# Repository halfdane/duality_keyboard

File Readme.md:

# The Duality Keyboard

Generated using ergogen:

There are two options to generate this:
- copy the content of `config/duality_keyboard.yaml` into https://ergogen.cache.works/ and start fiddling
- run `npm install` and `npm run start` (or `npm run watch` for continuous build)

# Install qmk
https://docs.qmk.fm/#/getting_started_make_guide

pamac install qmk

`sudo pacman -Sy base-devel gcc unzip wget zip avr-gcc avr-binutils avr-libc dfu-util arm-none-eabi-gcc arm-none-eabi-binutils arm-none-eabi-newlib git dfu-programmer dfu-util`

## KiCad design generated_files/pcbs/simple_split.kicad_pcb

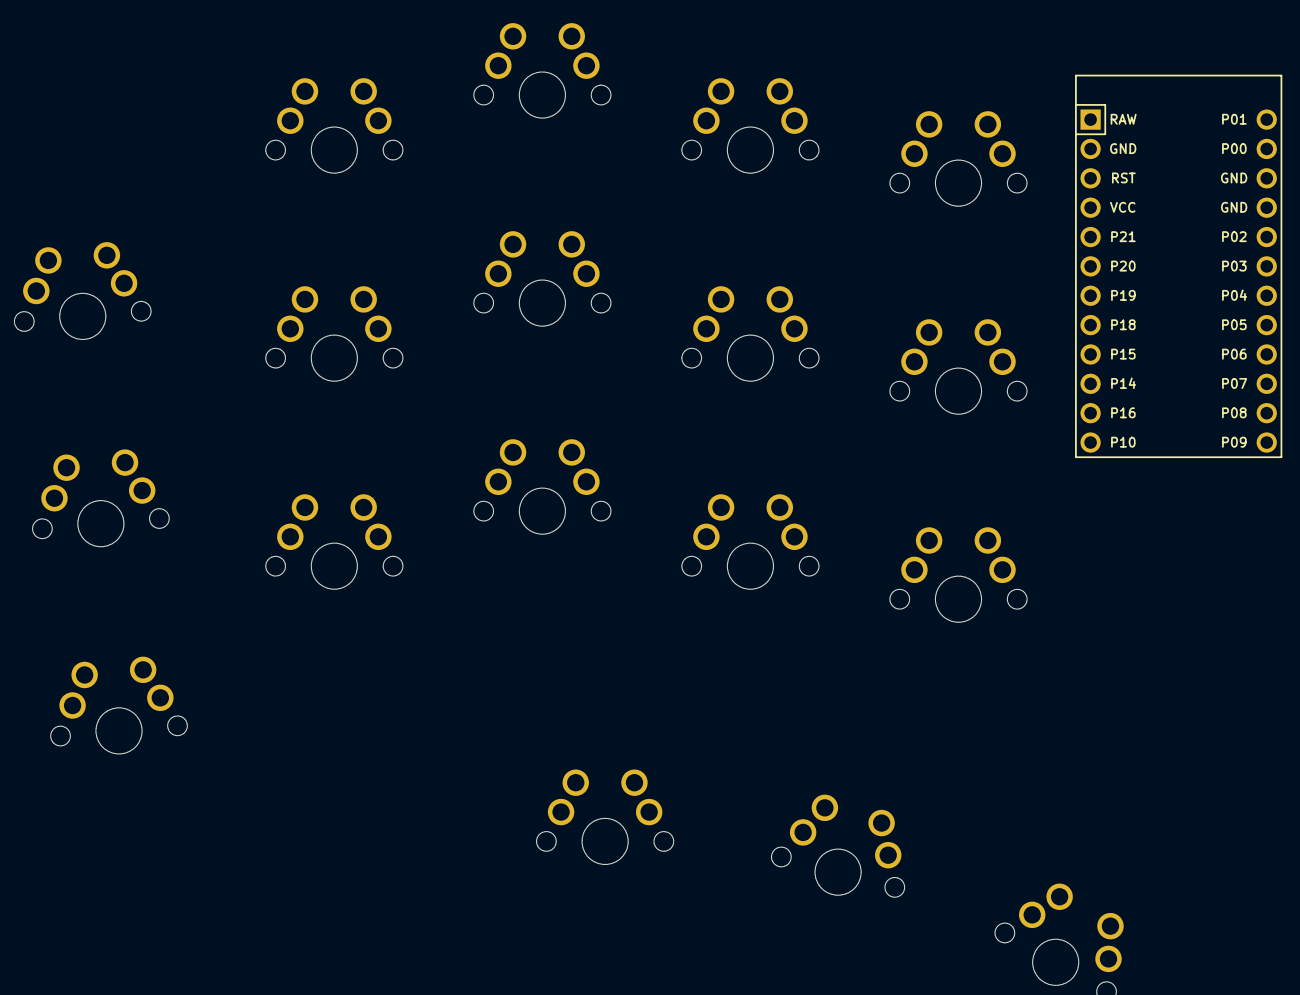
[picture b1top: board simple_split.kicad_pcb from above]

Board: 2 copper layers, 19 parts (0 on the bottom side), 18 nets, no tracks yet.

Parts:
MCU1: ProMicro
S1, S2, S3, S4, S5, S6, S7, S8, S9, S10, S11, S12, S13, S14, S15, S16, S17, S18: MX

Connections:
GND: MCU1.2, MCU1.15, MCU1.16, S1.1, S2.1, S3.1, S4.1, S5.1, S6.1, S7.1, S8.1, S9.1, S10.1, S11.1, S12.1, S13.1, S14.1, S15.1, S16.1, S17.1, S18.1
matrix_index_bottom: MCU1.20, S10.2
matrix_index_home: MCU1.12, S11.2
matrix_index_top: MCU1.6, S12.2
matrix_inner_bottom: MCU1.21, S13.2
matrix_inner_home: MCU1.13, S14.2
matrix_inner_top: MCU1.5, S15.2
matrix_middle_bottom: MCU1.19, S7.2
matrix_middle_home: MCU1.11, S8.2
matrix_middle_top: MCU1.7, S9.2
matrix_pinky_bottom: MCU1.17, S1.2
matrix_pinky_home: MCU1.9, S2.2
matrix_pinky_top: MCU1.22, S3.2
matrix_ring_bottom: MCU1.18, S4.2
matrix_ring_home: MCU1.10, S5.2
matrix_ring_top: MCU1.8, S6.2
thumb_reachy: MCU1.24, S18.2
thumb_tucky: MCU1.23, S16.2

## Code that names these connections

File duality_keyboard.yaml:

# `U` is a predefined unit of measure that means 19.05mm, which is MX spacing
points:
  zones:
    matrix:
      anchor:
        rotate: 5
      columns:
        pinky:
          spread: 1.1cx
        ring:
          rotate: -5
          stagger: 0.66U
          spread: 1.1cx
        middle:
          stagger: 0.25U
          spread: 1.05cx
        index:
          stagger: -0.25U
          spread: 1.05cx
        inner:
          stagger: -0.15U
          spread: 1.05cx
      rows:
        bottom.padding: 1.05cx
        home.padding: 1.05cx
        top.padding: 1.05cx
    thumb:
      anchor:
        ref: matrix_index_bottom
        shift: [-0.4U, -1.25U]
        rotate: 0
      columns:
        tucky:
          key.name: thumb_tucky
        middle:
          key.name: thumb_middle
          origin: [-0.5U, -0.3U]
          rotate: -15
        reachy:
          spread: U
          rotate: -15
          origin: [-0.5U, -0.3U]
          key.name: thumb_reachy
  key:
    footprints:
      - type: mx
        nets:
          from: GND
          to: =name
        params:
          reverse: true
          keycaps: false
outlines:
  exports:
    plate:
      - type: rectangle
        size: [150, 130]
        anchor.shift: [0, -40]
        corner: 10
    keys:
      - type: keys
        side: left
        size: [18,17]
        corner: 1
    touchpad:
      - type: circle
        radius: 19
        anchor.shift: [127, 25]
    intersected_outline:
      - +plate
      - -keys
      - -touchpad
pcbs:
  simple_split:
    footprints:
      - type: promicro
        anchor:
          - ref: matrix_inner_home
            shift: [1U, 0.5U]
            rotate: -90
        nets:
          P7: matrix_pinky_top
          P18: matrix_ring_top
          P19: matrix_middle_top
          P20: matrix_index_top
          P21: matrix_inner_top
          P15: matrix_pinky_home
          P14: matrix_ring_home
          P16: matrix_middle_home
          P10: matrix_index_home
          P1: matrix_inner_home
          P2: matrix_pinky_bottom
          P3: matrix_ring_bottom
          P4: matrix_middle_bottom
          P5: matrix_index_bottom
          P6: matrix_inner_bottom
          P8: thumb_tucky
          P9: thumb_reachy

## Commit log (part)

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2022-06-13 don't add generated files again
2022-06-13 remove generated files from git
2022-06-13 now with touchpad and a plate
2022-06-13 initial layout
2022-06-13 add the right-sized switch holes and a shaped switch plate
2022-06-13 add a little bit of space between keys
2022-06-13 Simple readme
2022-06-14 move trackpad closer to keys
2022-06-14 introduce entry to cable tunnel
2022-06-14 make touchpad-hole slightly larger
2022-06-14 add screw holes
2022-06-14 adjust readme
2022-06-21 use smaller footprint for keys
2022-06-21 reposition keywell and promicro after using smaller caps
2022-09-14 rethink the shape
2022-09-23 enough space for rp2040 zero
2022-09-26 reduce border so it does'nt get **huge**
2022-10-19 ordered the plate at laserboost
2024-05-25 better build pipeline
2024-05-25 several layers and an a3 cutout example
2024-05-27 remove stabilizer sticks
2024-05-27 decide hole sizes
2024-05-29 parameterize symbol
2024-06-02 documentation and layer preparation
2024-06-02 adjust to choc dimensions
2024-06-02 clean up choc top frame
2024-06-07 introduce connector holes
2024-06-08 all layers defined plus some cleanup
2024-06-08 include space for trackpad
2024-06-08 prepare second test burn
2024-06-13 adjust connectors and add touchpad magnet
2024-06-13 add more magnets to the top layers
2024-06-13 adjust rp2040 cutout to keep solder pads usable
2024-06-13 top layer of switch pad doesn't have screw holes - hopefully they can stay below
2024-06-13 consolidate some layers
2024-06-13 new voronoi pattern
2024-06-14 prepare next cut
2024-06-15 simple spoilboard markers to help positioning and focus
2024-06-20 doubling up veneer sheets reduces layer count
2024-06-20 resize the keyboard, change the design and place several components at the right position
2024-06-20 some more connector fiddling
2024-06-20 reposition thumb screws
2024-06-21 adjust magnets
2024-06-21 adjust touchpad
2024-06-21 first experiment with cirque case
2024-06-21 touchpad case
2024-06-26 fix outline where circle and thumb cluster meet
2024-06-29 finetuning the trackpad
2024-06-29 next lasering
2024-07-05 add a little recess for switches to clamp onto
2024-07-05 additional switchplate layer without recess, just in case the recesses are too much
2024-07-30 move files for case to its own subdir
2024-07-30 kmk firmware that kinda mostly works
2024-07-30 some documentation on the kmk firmware
2024-12-29 all layers work as expected now
2025-01-02 add some inertial mouse cursor and inertial circular scrolling
2025-01-02 remove timeouts on thumb keys - they were accidentally introduced by the chords, but never actually useful
2025-01-02 extract tap detector in order to realize a tap-drag gesture
2025-01-03 tap detection with multiple taps and tap-drag detection. Tap-tap-drag doesn't work
2025-01-03 prepare automatic mounting
2025-01-03 tap and drag detection works now for all amounts of taps before a drag happens
2025-01-03 add simple debouncing because touchpad is noisy
2025-01-03 tap-drag gestures don't have an additional mouseclick anymore
2025-01-04 simple taps are not so sluggish anymore, but double taps don't work anymore :/
2025-01-04 don't use tap dance on a letter
2025-01-05 taps, holds and double taps work, but only when tapping very quickly
2025-01-05 disable automounting unless a thumb key is pressed
2025-01-05 automatic holding from the touchpad has interferred with keyboard mouse buttons. Reverting everything to simply support tap gestures.
2025-01-09 allow access to logs
2025-01-09 when following logs, just try to access any device that's there :/
2025-01-09 don't try to register as keyboard explicitely - it breaks multimedia keys
2025-01-10 extract fling behaviour
2025-01-10 keep moving the cursor on the previous trajectory if the touch is at the outer reaches of the touchpad.
2025-01-11 include newer version of circuitpython - both versions seem to work equally good, so i'll probably switch to the newer version completely eventually
2025-01-11 Let's see if this thing doesn't work with zmk as well
2025-01-12 use own zmk fork with rp2040 zero support
2025-01-12 be able to wake laptop from sleep
2025-01-12 wait a tiny bit before trying to mount the board
2025-01-13 switch to matrix layout to introduce zmk studio capabilities
2025-01-13 create full particle layout and introduce splitting
2025-01-13 access to zmk studio works
2025-01-13 enter venv before trying to compile
2025-01-13 matrix transform resembles soldering matrix now
2025-01-18 automatic cursor movement at the corners doesn't really work as is
2025-01-18 prepare for miryokufication
2025-01-18 particle only has two thumb keys
2025-01-18 fix split definition
2025-01-18 let's see if the split wired branch works
2025-01-19 maybe both sides want a name?
2025-01-19 be able to fiddle with uart pins - I have the feeling that I may have switched RX and TX
2025-01-20 turns out the rx and tx line weren't crossed :/
2025-01-20 matrix definition finalized
2025-01-20 switch to vanilla miryoky=u for ferris
2025-01-20 naming the keyboard happens equally for both sides
2025-01-22 reduce uart speed for communication between halves to stabilize the connection
2025-01-23 ignore logs
2025-01-23 new zephyr fix doesn't depend on reduced connection speed
2025-01-23 clean up whitespace
2025-01-23 ignore imported module
2025-01-23 fetch the uart fifo changes for zephyr
2025-01-23 include cirque module
2025-01-23 seem like combo-config is ignored if it's defined in the global config, but works when defined in the sider
2025-01-23 configure i2c pins for cirque communication
2025-01-23 move config from one place to another
2025-01-23 add central and peripheral configuration of cirqui
2025-01-23 maybe putting the i2c=y everywhere helps?
2025-01-23 reducing i2c speed at least allows the board to boot
2025-01-23 make right side central, so cirque can be on central
2025-01-24 adjust miryoku mouse behaviour
2025-01-24 directly handle miryoku without detour through another .h file
2025-01-25 Use own miryoku fork instead of patching it in place
2025-01-25 No need to patch miryoku after switching to own fork
2025-01-28 turns out you can't just invent numbers here
2025-01-28 turns out that the global configuration lives somewhere else
2025-01-28 reactivate cirque configuration - it wasn't the reason for the error messages
2025-01-28 remove obsolete file
2025-01-28 cirque works with dr pin
2025-01-29 finetuning for cirque behavious
2025-01-30 more fiddling with cirque
2025-02-09 remove all stuff at once when cleaning
2025-02-09 fix instability that's introduced with the log snippet by increasing the stack size
2025-02-09 reduce temp layer timeout
2025-02-09 hu, what's the nvs stuff doing there?
2025-02-09 disable zmk studio support for now
2025-02-12 enable absolute mode in cirque
2025-02-12 adjust logging
2025-02-21 deactivate all cirque functionality to test newest changes
2025-02-22 reactivate cirque and gestures
2025-02-22 use input processor to translate absolute to relative
2025-02-24 activate circular scroll
2025-02-24 configure clamp values for absolute mode
2025-02-25 increase sensitive zone for circular scroll
2025-03-08 include zephyr's west.yml
2025-03-15 include cirque only on right side.
2025-03-15 add build.yaml, to eventually use github actions
2025-04-21 ignore generated directories
2025-04-21 return to zmk main, now that the wired split code is merged
2025-07-17 initial fitting test print
2025-07-18 first steps towards the duality:wave keyboard
2025-07-21 dongle works
2025-07-26 use display names for dongle resets to make them easier identifiable in script
2025-08-03 more experiments with freecad
2025-08-03 first attempts with build123d
2025-08-08 getting the hang of build123d
2025-08-11 position model right side up and add bottom plate
2025-08-30 be able to knurl a face
2025-09-01 add powerswitch
2025-09-01 lift xiao away from bottom to make usb hole more stable
2025-09-01 lift power switch away from bottom
2025-09-01 adjust size of clipper-pin and reposition keys so as to not interfere with the walls
2025-09-02 add shadowline and chamfers
2025-09-09 prototype finished
2025-09-09 adjust choc keycap sizing
2025-09-12 with knurl
2025-09-14 simplify switch positioning
2025-09-14 extract switch positions into its own file
2025-09-14 extract outline and simplify dimensions
2025-09-14 xiao positioning and cuts for keyplate
2025-09-14 simplify key cutouts in keyplate
2025-09-14 add depression for connections
2025-09-14 add little protrusions to hold the connectors
2025-09-14 adjust the little protrusions as well as the connector positions
2025-09-15 extract knurl
2025-09-15 translate switch positions globally instead of locally
2025-09-15 add first attempt at keywell
2025-09-15 add first attempt at bottom plate
2025-09-15 adjust knurling to be correctly oriented
2025-09-15 add knurling to remaining faces
2025-09-17 add holders for bottom
2025-09-19 make outline smoother by using 1d objects instead of stacking 2d objects
2025-09-19 usb-cutter should cut in both directions
2025-09-19 add ribs to bottom and finalize fit between keyplate and bottom
2025-09-19 add recess into bottom for bottom-holders from keyplate
2025-09-20 finalize bottom holders and bumpers, as well as fix some collisions between parts.
2025-09-20 add clips to hold the bottom
2025-09-21 make bottom_holder a tiny bit more stable
2025-09-21 make tighter fit between bottom and keyplate
2025-09-21 adjust bottom holders and the inner wall of the keyplate
2025-09-22 refactor key positioning and outline
2025-09-22 make keyplate's inner wall thicker
2025-09-22 change dimension of switches to vectors
2025-09-22 change dimension of outline to vector
2025-09-22 change dimension of xiao to vector and refactor a bit
2025-09-23 put outer wall on the bottom instead of on the keyplate
2025-09-23 adjust xiao positioning and usb holes
2025-09-24 add physical support for xiao as well as reset button
2025-09-24 make case slimmer by recessing switch posts into bottom-plate, along with necessary adjustments. Introduce powerswitch
2025-09-25 simplify keys
2025-09-25 again fiddling with the positioning
2025-09-25 use fewer magic numbers for outline construction
2025-09-27 add manual fillet between pinkie and ring
2025-09-27 get rid of ribs on bottom plate and refactor the reset lever
2025-09-27 small adjustments for slicer
2025-09-28 refactor clips so that one of them can be much larger
2025-09-29 refactor keywell
2025-09-29 refactor case dimensions
2025-09-29 add edge to hold keyplate in z-place
2025-09-29 simplify clip-design and add holding-clips for plates.
2025-09-29 refactor clips
2025-09-29 make long clips even longer
2025-09-29 add taper to long clips
2025-09-30 sculpt thumb cluster
2025-09-30 refactor visual debugging
2025-10-01 refactor bumper holder dimensions and cleanup extrusions
2025-10-02 reposition xiao and power switch, refactor connector depressions
2025-10-02 pin holes
2025-10-02 ad pin models
2025-10-03 adjust some dimensions
2025-10-03 adjust outline because battery wouldn't fit otherwise. Add battery and magnets
2025-10-03 adjust wire connector to xiao to account for new y size
2025-10-03 using a nail as a pin, which required a bit of shuffling
2025-10-04 add symbol to top of keywell
2025-10-04 make slightly more room for one of the magnets
2025-10-04 ad a little recess below the xiao to make space for components
2025-10-04 rename switch file
2025-10-04 add cherry model
2025-10-04 make outline and key positions parameterizable so other switches and caps can be supported as well
2025-10-04 expose more attributes through interface
2025-10-04 actually try to build it for cherry
2025-10-13 reposition pin
2025-10-13 derive keywell from key positions
2025-10-23 make outlines more dependent on key positions
2025-11-03 switch fully to ergogen based layout
2025-11-04 fix keywell
2025-11-04 looks good now
2025-11-07 create prototype
2025-11-07 put switch clearance not into switch but when cutting out the hole
2025-11-08 skip top edge when trying to find good places for longer snap clips
2025-11-08 fix edge orientation of outlines and all subsequent cleanups
2025-11-08 introduce parent class for case dimensions as well as a positioning of space invaders
2025-11-10 place pin a tiny bit more topwards
